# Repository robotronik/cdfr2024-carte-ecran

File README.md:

# cdfr2024-carte-ecran

Carte PCB pour l'écran du robot

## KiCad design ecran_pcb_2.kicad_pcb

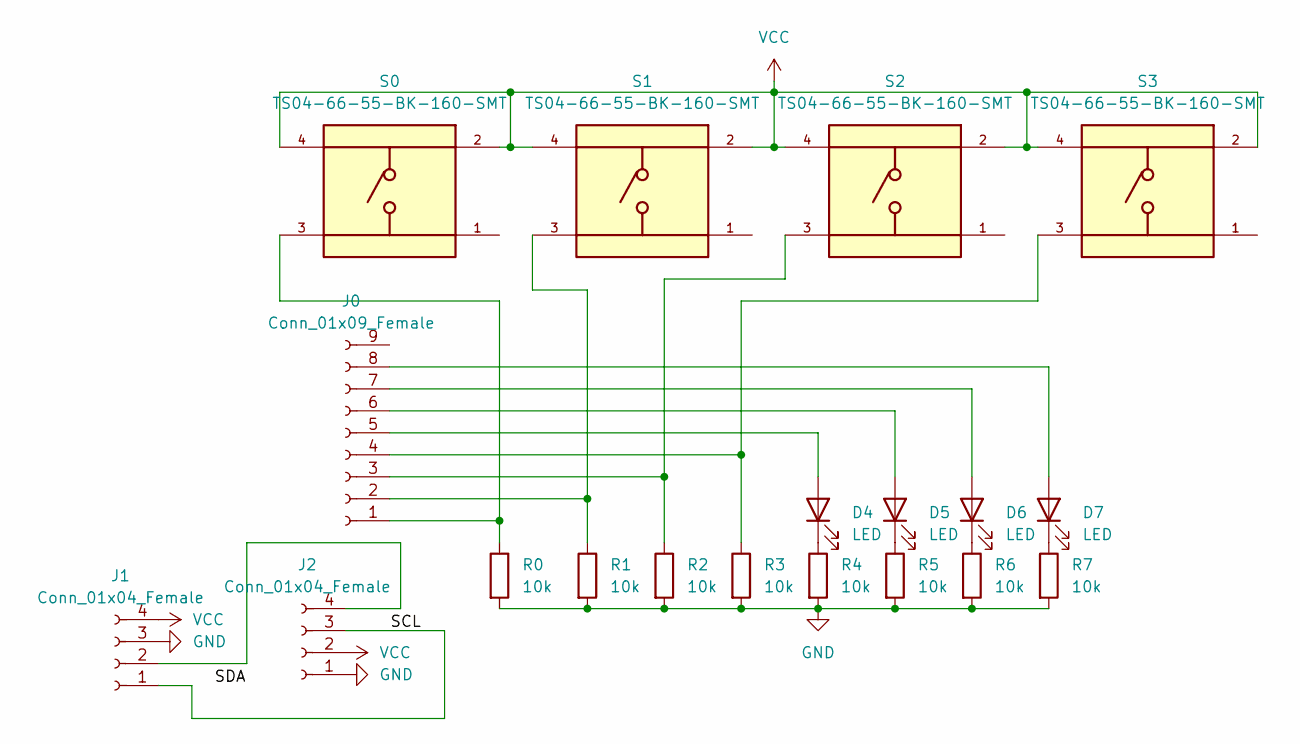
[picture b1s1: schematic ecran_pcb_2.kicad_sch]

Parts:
D4, D5, D6, D7: LED; LED_Rectangular_W3.0mm_H2.0mm
J0: Conn_01x09_Female; PinSocket_1x09_P2.54mm_Vertical
J1, J2: Conn_01x04_Female; PinSocket_1x04_P2.54mm_Vertical
R0, R1, R2, R3, R4, R5, R6, R7: 10k; R_1206_3216Metric_Pad1.30x1.75mm_HandSolder
S0, S1, S2, S3: TS04-66-55-BK-160-SMT; SW_TS04-66-55-BK-160-SMT; PARTREV 1.0

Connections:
/SCL: J1.1, J2.3
GND: J1.3, J2.1, R0.2, R1.2, R2.2, R3.2, R4.2, R5.2, R6.2, R7.2
unnamed: D4.1 (K), R4.1
unnamed: D4.2 (A), J0.5
unnamed: D5.1 (K), R5.1
unnamed: D5.2 (A), J0.6
unnamed: D6.1 (K), R6.1
unnamed: D6.2 (A), J0.7
unnamed: D7.1 (K), R7.1
unnamed: D7.2 (A), J0.8
unnamed: J0.1, R0.1, S0.3
unnamed: J0.2, R1.1, S1.3
unnamed: J0.3, R2.1, S2.3
unnamed: J0.4, R3.1, S3.3
unnamed: J1.2, J2.4
VCC: J1.4, J2.2, S0.2, S0.4, S1.2, S1.4, S2.2, S2.4, S3.2, S3.4

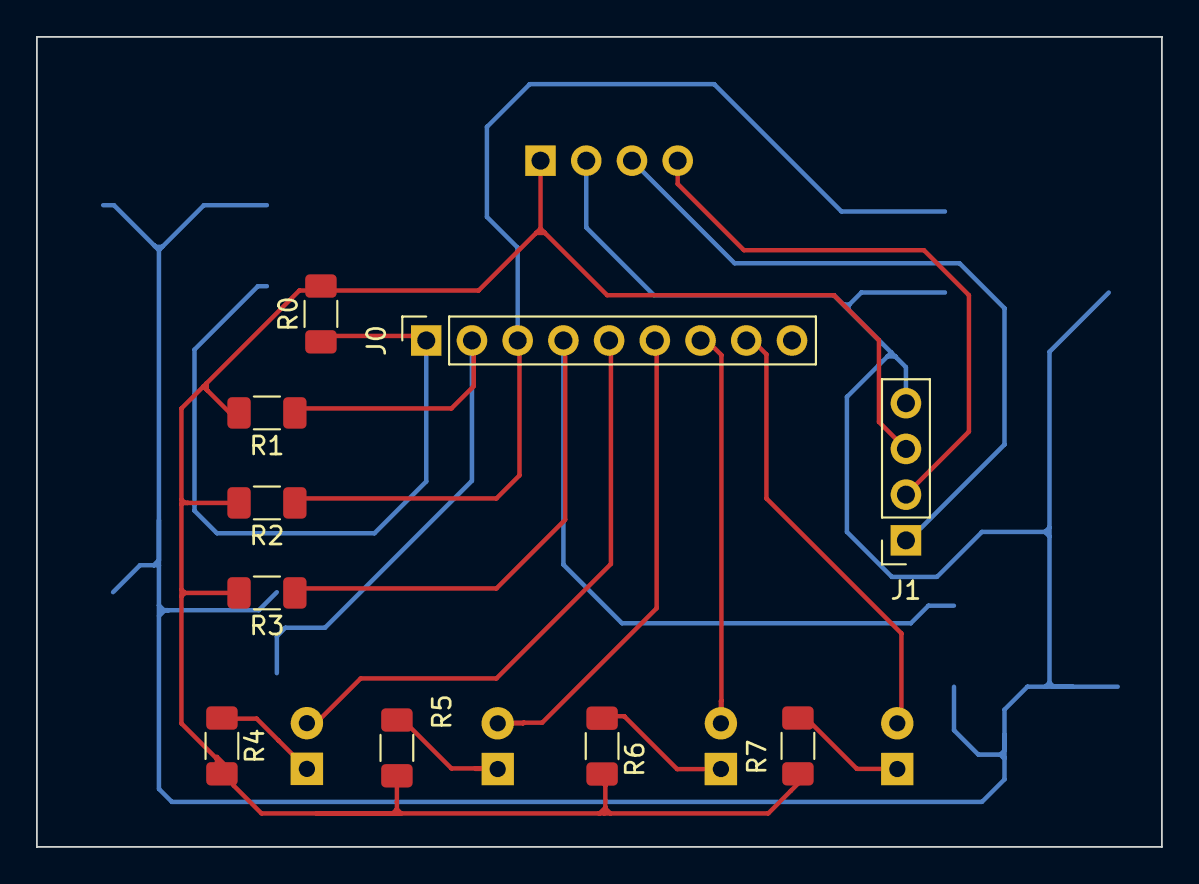
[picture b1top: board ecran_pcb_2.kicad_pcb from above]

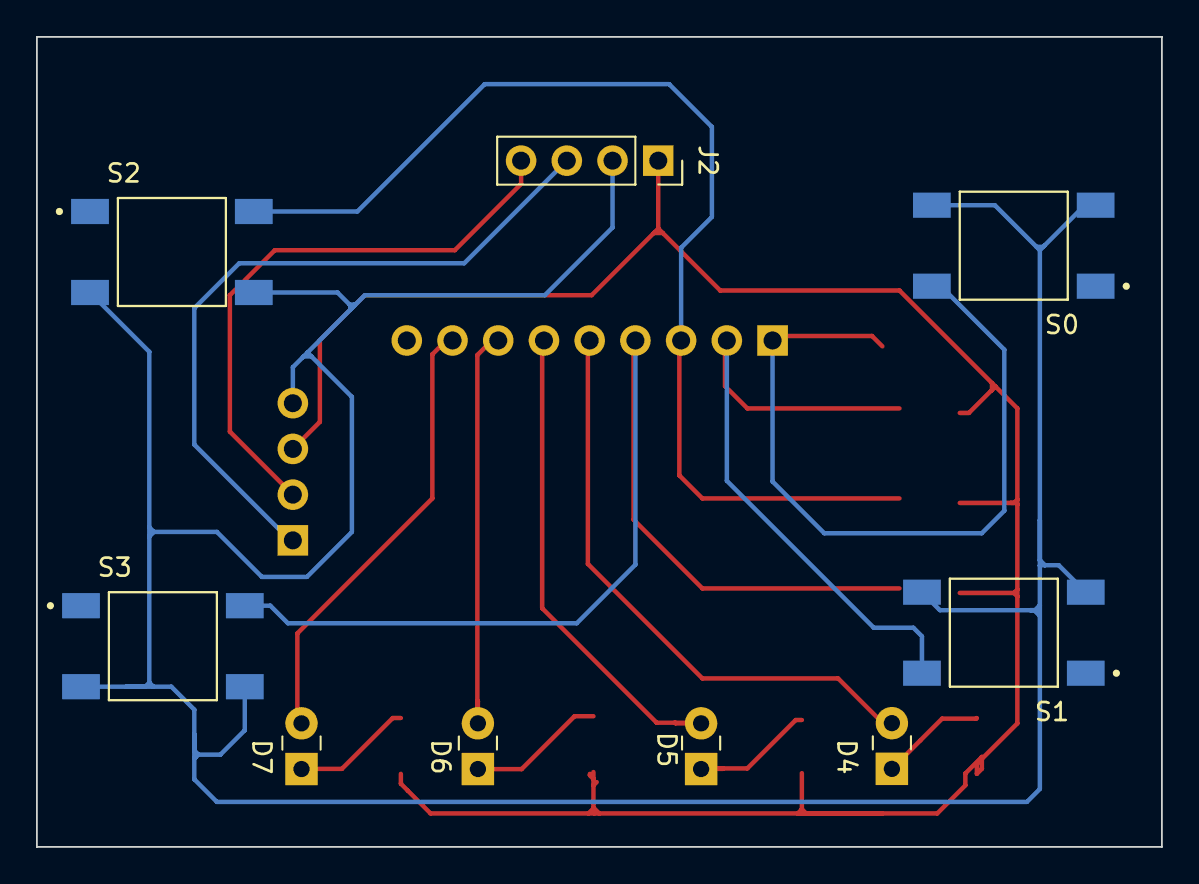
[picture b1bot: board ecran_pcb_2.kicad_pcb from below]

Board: 2 copper layers, 62.5 x 45.0 mm, 19 parts (9 on the bottom side), 16 nets.

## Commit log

2024-04-19 Add files via upload
    first git
